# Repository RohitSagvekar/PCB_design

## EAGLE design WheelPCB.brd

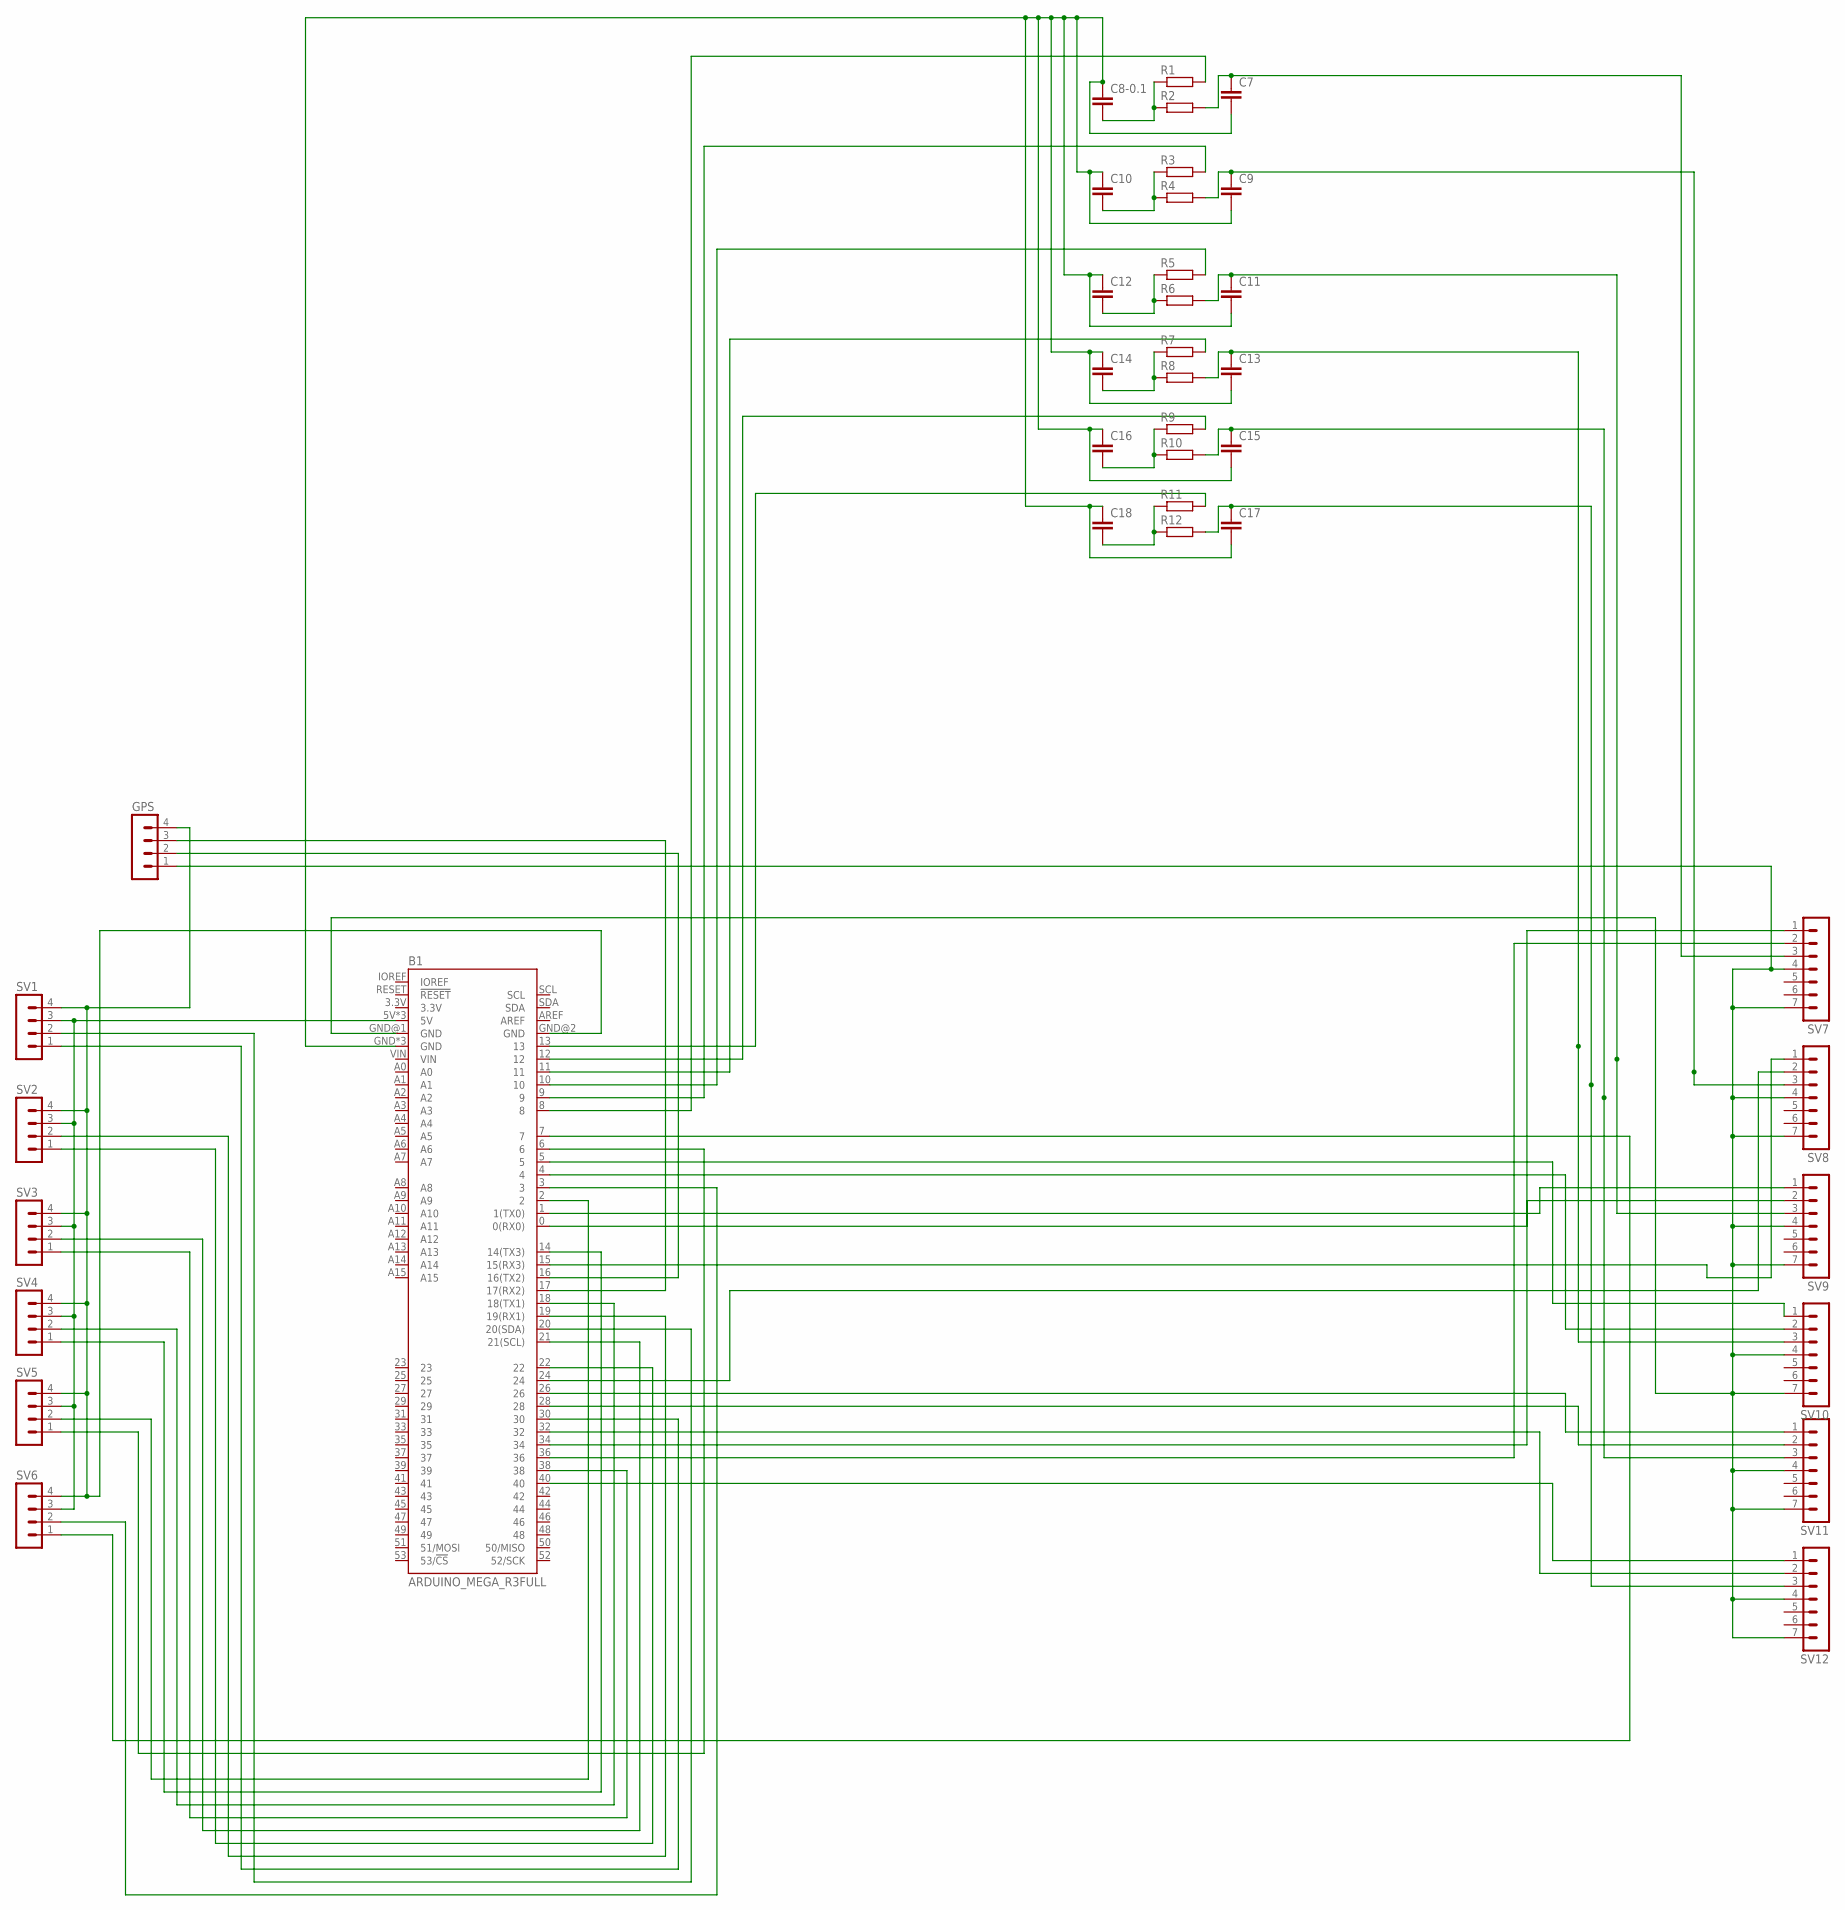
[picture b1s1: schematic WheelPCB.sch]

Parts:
B1: ARDUINO_MEGA_R3FULL; ARDUINO_MEGA_NO_SILK
C7, C8-0.1, C9, C10, C11, C12, C13, C14, C15, C16, C17, C18: C2.5/5; C2.5-5
GPS: MA04-1
R1, R2, R3, R4, R5, R6, R7, R8, R9, R10, R11, R12: R-EU_0207/10; 0207/10
SV1, SV2, SV3, SV4, SV5, SV6: MA04-1
SV7, SV8, SV9, SV10, SV11, SV12: MA07-1

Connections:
unnamed: B1.GND@1 (GND), GPS.1, SV7.4, SV7.7, SV8.4, SV8.7, SV9.4, SV9.7, SV10.4, SV10.7, SV11.4, SV11.7, SV12.4, SV12.7
unnamed: C13.1, R8.2, SV10.3
unnamed: B1.13, R11.2
unnamed: C15.1, R10.2, SV11.3
unnamed: C11.1, R6.2, SV9.3
unnamed: C9.1, R4.2, SV8.3
unnamed: C17.1, R12.2, SV12.3
unnamed: B1.4, SV10.2
unnamed: B1.5, SV10.1
unnamed: B1.7, SV6.1
unnamed: B1.6, SV5.1
unnamed: B1.3, SV6.2
unnamed: B1.2, SV5.2
unnamed: B1.1 (1(TX0)), SV9.1
unnamed: B1.0 (0(RX0)), SV9.2
unnamed: B1.15 (15(RX3)), SV8.1
unnamed: B1.24, SV8.2
unnamed: B1.40, SV12.1
unnamed: B1.32, SV12.2
unnamed: B1.26, SV11.1
unnamed: B1.28, SV11.2
unnamed: B1.34, SV7.1
unnamed: B1.36, SV7.2
unnamed: B1.14 (14(TX3)), SV4.1
unnamed: B1.18 (18(TX1)), SV4.2
unnamed: B1.38, SV3.1
unnamed: B1.21 (21(SCL)), SV3.2
unnamed: B1.22, SV2.1
unnamed: B1.19 (19(RX1)), SV2.2
unnamed: B1.30, SV1.1
unnamed: B1.20 (20(SDA)), SV1.2
unnamed: B1.5V, B1.5V@1 (5V), B1.5V@2 (5V), SV1.3, SV2.3, SV3.3, SV4.3, SV5.3, SV6.3
unnamed: B1.GND@2 (GND), GPS.4, SV1.4, SV2.4, SV3.4, SV4.4, SV5.4, SV6.4
unnamed: B1.16 (16(TX2)), GPS.2
unnamed: B1.17 (17(RX2)), GPS.3
unnamed: B1.8, R1.2
unnamed: C8-0.1.2, R1.1, R2.1
unnamed: B1.10, R5.2
unnamed: C7.1, R2.2, SV7.3
unnamed: C10.2, R3.1, R4.1
unnamed: B1.9, R3.2
unnamed: C12.2, R5.1, R6.1
unnamed: C14.2, R7.1, R8.1
unnamed: B1.11, R7.2
unnamed: C18.2, R11.1, R12.1
unnamed: B1.12, R9.2
unnamed: C16.2, R9.1, R10.1
unnamed: B1.GND, B1.GND@3 (GND), B1.GND@4 (GND), C7.2, C8-0.1.1, C9.2, C10.1, C11.2, C12.1, C13.2, C14.1, C15.2, C16.1, C17.2, C18.1

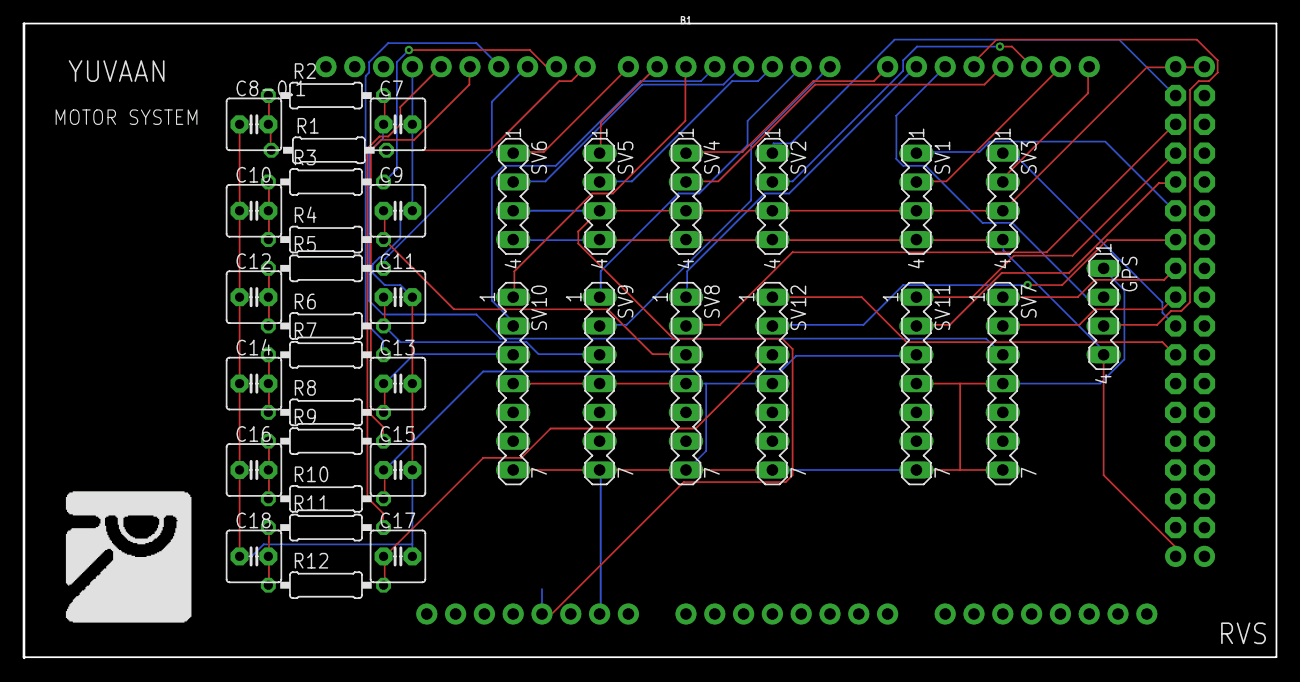
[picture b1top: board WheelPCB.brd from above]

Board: 2 copper layers, 110.5 x 56.0 mm, 38 parts (0 on the bottom side), 48 nets.

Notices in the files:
parts and their libraries:
SparkFun-Boards: Licensing: Creative Commons ShareAlike 4.0 International - https://creativecommons.org/licenses/by-sa/4.0
